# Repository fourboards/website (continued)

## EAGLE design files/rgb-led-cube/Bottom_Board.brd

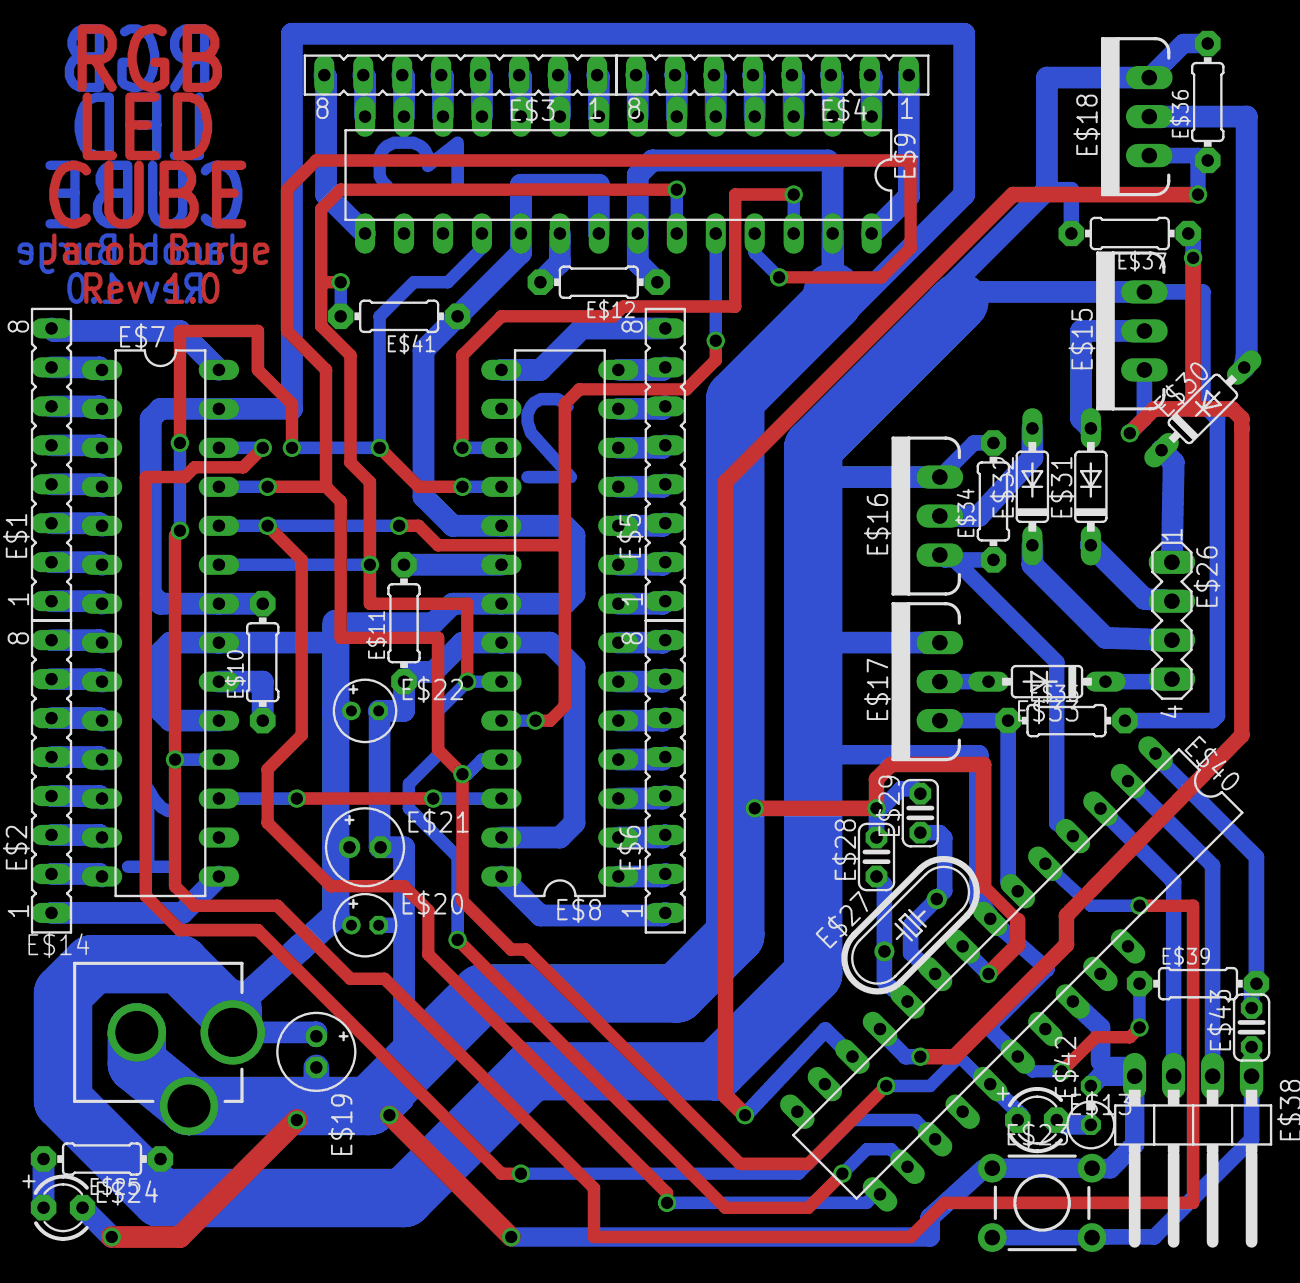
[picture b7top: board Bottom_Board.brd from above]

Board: 2 copper layers, 43 parts (0 on the bottom side), 83 nets.

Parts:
E$1, E$2, E$3, E$4, E$5, E$6: FE08
E$7, E$8, E$9: DIL28-3
E$10, E$11, E$12, E$25, E$34, E$35, E$36, E$37, E$39, E$41: 0204/7
E$13, E$24: LED3MM
E$14: DCJACK_2MM_PTH
E$15, E$16, E$17, E$18: TO220V
E$19, E$21: E2-5
E$20, E$22: E1,8-4
E$23: TACTILE-PTH
E$26: MA04-1
E$27: HC49/S
E$28, E$29, E$43: C025-024X044
E$30, E$31, E$32, E$33: DIODE_DO35-7
E$38: 1X04/90
E$40: DIP_28_MOD
E$42: 0309V

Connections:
S$1: E$1.7, E$7.1
S$2: E$1.6, E$7.2
S$3: E$1.5, E$7.3
S$4: E$1.4, E$7.4
S$5: E$1.3, E$7.5
S$6: E$1.2, E$7.6
S$7: E$1.1, E$7.7
S$8: E$2.8, E$7.8
S$9: E$2.7, E$7.9
S$10: E$2.6, E$7.10
S$11: E$2.5, E$7.11
S$12: E$2.4, E$7.12
S$13: E$2.3, E$7.13
S$14: E$2.2, E$7.14
S$15: E$2.1, E$7.15
S$16: E$1.8, E$7.28
S$17: E$3.7, E$9.14
S$18: E$3.6, E$9.13
S$19: E$3.5, E$9.12
S$20: E$3.4, E$9.11
S$21: E$3.3, E$9.10
S$22: E$3.2, E$9.9
S$23: E$3.1, E$9.8
S$24: E$4.8, E$9.7
S$25: E$4.7, E$9.6
S$26: E$4.6, E$9.5
S$27: E$4.5, E$9.4
S$28: E$4.4, E$9.3
S$29: E$4.3, E$9.2
S$30: E$4.2, E$9.1
S$31: E$4.1, E$9.28
S$32: E$3.8, E$9.15
S$33: E$5.7, E$8.14
S$34: E$5.6, E$8.13
S$35: E$5.5, E$8.12
S$36: E$5.4, E$8.11
S$37: E$5.3, E$8.10
S$38: E$5.2, E$8.9
S$39: E$5.1, E$8.8
S$40: E$6.8, E$8.7
S$41: E$6.7, E$8.6
S$42: E$6.6, E$8.5
S$43: E$6.5, E$8.4
S$44: E$6.4, E$8.3
S$45: E$6.2, E$8.1
S$46: E$6.3, E$8.2
S$47: E$6.1, E$8.28
S$48: E$5.8, E$8.15
S$49: E$7.22, E$7.27, E$9.22, E$9.27, E$10.2, E$12.1
S$50: E$9.20, E$12.2
S$51: E$8.20, E$11.2
S$52: E$7.20, E$10.1
S$56: E$14.GND, E$14.GNDBREAK, E$24.K
S$57: E$7.26, E$40.17
S$59: E$24.A, E$25.2
S$60: E$27.1, E$28.1
S$61: E$27.2, E$29.1
S$62: E$18.1, E$36.1
S$64: E$17.1, E$35.1
S$65: E$16.1, E$34.1, E$40.4
S$66: E$26.1, E$30.C
S$67: E$18.2, E$30.A
S$68: E$15.2, E$31.A
S$69: E$26.2, E$31.C
S$70: E$26.3, E$32.C
S$71: E$16.2, E$32.A
S$72: E$17.2, E$33.A
S$73: E$26.4, E$33.C
S$75: E$7.19, E$7.21, E$8.19, E$8.21, E$9.19, E$9.21, E$14.PWR, E$17.3, E$18.3, E$19.+, E$20.+, E$21.+, E$22.+, E$25.1, E$36.2, E$37.2, E$39.1
S$77: E$23.3, E$23.4, E$38.1, E$43.1
S$81: E$23.1, E$23.2, E$38.4, E$40.22, E$42.2
S$82: E$7.25, E$8.25, E$9.25, E$13.A, E$40.19
S$83: E$13.K, E$42.1
S$84: E$28.2, E$29.2
S$85: E$7.18, E$8.18, E$9.18, E$40.5
S$86: E$15.3, E$35.2
S$89: E$15.1, E$37.1
S$90: E$7.17, E$8.26
S$91: E$8.17, E$9.26
S$92: E$7.24, E$8.24, E$9.24, E$40.15
S$93: E$7.23, E$8.23, E$9.23, E$40.16, E$41.2
S$94: E$8.22, E$8.27, E$11.1, E$22.-
S$95: E$39.2, E$43.2

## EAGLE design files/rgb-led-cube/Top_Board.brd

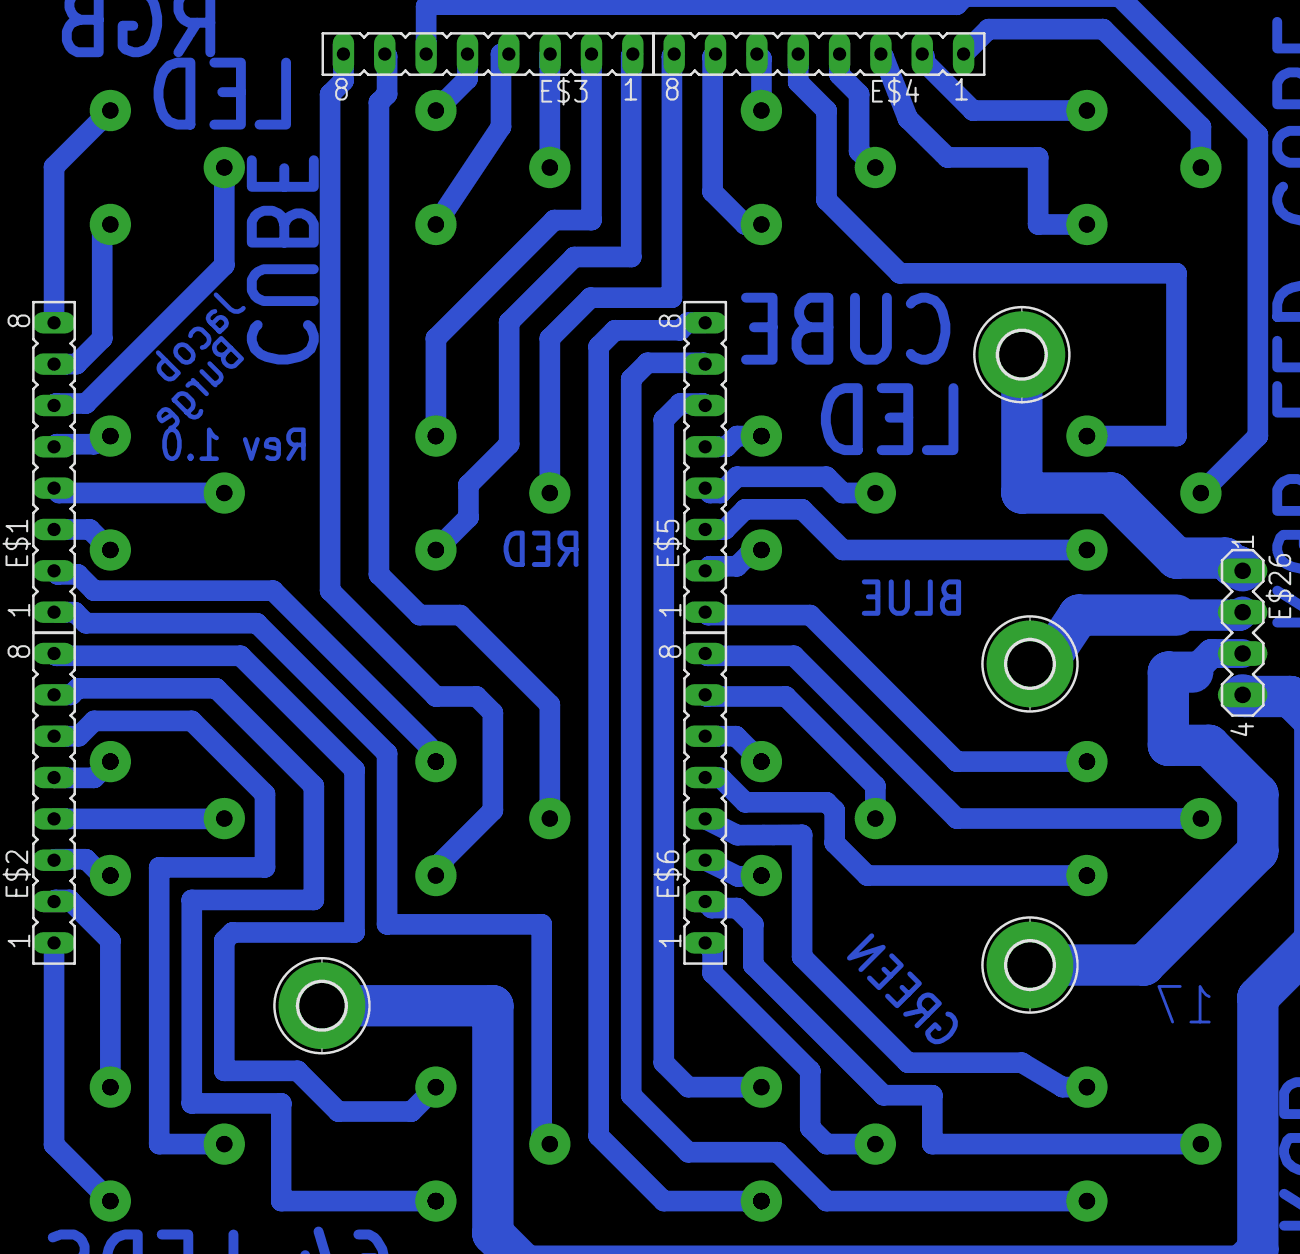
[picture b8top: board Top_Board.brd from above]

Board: 2 copper layers, 27 parts (0 on the bottom side), 52 nets.

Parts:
E$1, E$2, E$3, E$4, E$5, E$6: FE08
E$7, E$9, E$10, E$27: 2,8-PAD
E$8, E$11, E$12, E$13, E$14, E$15, E$16, E$17, E$18, E$19, E$20, E$21, E$22, E$23, E$24, E$25: RGB_LED
E$26: MA04-1

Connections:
S$12: E$1.5, E$11.P$2
S$41: E$1.6, E$8.P$3
S$42: E$1.7, E$8.P$1
S$43: E$1.8, E$8.P$2
S$44: E$3.5, E$12.P$2
S$45: E$3.4, E$12.P$1
S$46: E$3.3, E$12.P$3
S$47: E$3.2, E$14.P$2
S$48: E$3.1, E$14.P$1
S$49: E$4.8, E$14.P$3
S$50: E$4.6, E$15.P$2
S$51: E$4.7, E$15.P$1
S$53: E$4.4, E$15.P$3
S$54: E$4.3, E$16.P$1
S$55: E$4.2, E$16.P$2
S$56: E$4.1, E$16.P$3
S$57: E$1.4, E$11.P$3
S$58: E$1.3, E$11.P$1
S$59: E$2.5, E$13.P$2
S$60: E$2.4, E$13.P$3
S$61: E$2.3, E$13.P$1
S$62: E$2.7, E$23.P$1
S$63: E$2.8, E$23.P$2
S$64: E$1.1, E$23.P$3
S$65: E$1.2, E$19.P$2
S$66: E$3.7, E$19.P$3
S$67: E$2.1, E$22.P$1
S$68: E$2.2, E$22.P$2
S$69: E$2.6, E$22.P$3
S$70: E$3.8, E$19.P$1
S$71: E$3.6, E$18.P$3
S$73: E$4.5, E$18.P$2
S$74: E$5.8, E$24.P$1
S$76: E$5.6, E$24.P$2
S$77: E$5.7, E$25.P$1
S$78: E$5.5, E$17.P$2
S$79: E$5.2, E$17.P$1
S$80: E$5.4, E$17.P$3
S$81: E$5.3, E$18.P$1
S$82: E$6.6, E$20.P$2
S$83: E$6.4, E$25.P$2
S$84: E$6.7, E$20.P$3
S$85: E$6.3, E$20.P$1
S$86: E$6.2, E$25.P$3
S$87: E$6.1, E$24.P$3
S$88: E$6.5, E$21.P$1
S$89: E$6.8, E$21.P$3
S$90: E$26.4, E$27.B2,8
S$91: E$5.1, E$21.P$2
S$92: E$9.B2,8, E$26.3
S$93: E$10.B2,8, E$26.2
S$107: E$7.B2,8, E$26.1

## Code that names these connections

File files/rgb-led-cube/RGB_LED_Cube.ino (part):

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
switch(layer){

case 1:    PORTD |= _BV(PD6); break;
case 2:    PORTD |= _BV(PD4); break;
case 3:    PORTD |= _BV(PD2); break;
case 4:    PORTD |= _BV(PD5); break;

} 
    
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
switch(layer){

case 1:    PORTD &= ~_BV(PD4); break;
case 2:    PORTD &= ~_BV(PD2); break;
case 3:    PORTD &= ~_BV(PD5); break;
case 4:    PORTD &= ~_BV(PD6); break;

}

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
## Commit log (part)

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2024-02-01 Creation from Junior template
2024-02-01 Importing HTML
2024-02-02 Added support for galleries, iframe and buttons
2024-02-04 Removed unused images
2024-02-04 Favicon
2024-02-04 Fixed link in start page
2024-02-04 Fixed missing images
2024-02-05 Fixed missing files
2024-02-27 Removed pink highlighting
2024-02-27 Made nav disappear on click
2024-02-27 Fixed favicon
2024-02-27 Implemented dynamic banner
2024-02-27 Made header static
2024-02-27 Fixed formatting
2024-02-27 Fixed URL
2024-02-27 Configured base url
2024-02-27 Fix for links/images
2024-02-27 Renamed images to lower case extensions
2024-02-27 Removed images
2024-02-27 Added lowercase images
2024-02-27 Fixed javascript links
2024-02-27 Fixed URL issues
2024-02-27 Further link fixes
2024-02-28 Fixed home button formatting
2024-02-28 Added support for buttons and fix local links in generation
2024-02-28 Stop banner changing in background
2024-02-28 Added filterihng tags for meta and arrows
2024-02-28 Support pages formatting
2024-02-28 Support for code blocks
2024-02-28 Touchpad support in page links
2024-02-28 Fixed broken images
2024-02-28 Apply correct links to images
2024-02-28 Fixed missing arrows and swapped direction
2024-02-28 Formatted PCBWay logo
2024-02-28 Removed Disqus
2024-02-28 Fixed image gallery order
2024-02-28 Added youtube
2024-02-28 Added missing youtube videos
2024-02-29 Create CNAME
2024-02-29 Updated for custom domain
2024-09-27 fix CVE-2024-47220 webrick vulnerability
2024-09-27 Security updates
2025-03-16 update nokogiri, uri and rexml to fix vulnerabilities
2025-03-26 fix nokogiri vulneribility
2025-08-11 security fix
2025-11-11 Remove drive links
2026-01-24 Update config
2026-04-20 security patch
